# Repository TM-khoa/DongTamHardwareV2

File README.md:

# Hardware Air Cleaning Machine Valve Controller

# Hardware library

Download hardware library at this [repository](https://github.com/TM-khoa/KicadHardwareLibrary.git)
# Hardware description
## Powersource
- The system board is powered by a dual power supply, the AM22 AC-DC converter, which outputs both 24VDC and 5VDC.
- The power for the MCUs, LoRa module, and RS485 needs to be regulated to 3.3V using the LD1117-3.3 regulator.
- Other components can use the 5V output from the AM22.
- Two terminals—one for 5V and one for 24V—can be used to power the system board from an external DC supply.

## Control valve and fault detect
Each output pin of the Output Expander 74HC595 is connected to the Gate pin of an N-channel MOSFET (SI2302). The Source pin is connected to a 0.5 Ohm shunt resistor and to ground, while the Drain pin is connected to one terminal of the valve. The other valve terminal is connected to the 24V power supply.
	
An LM324 Op-Amp samples the voltage drop across the shunt resistor (approximately 300mV). This voltage is compared to a reference voltage to detect faults. A valve error occurs if there is no voltage drop.

To control 16 valves, two cascaded 74HC595 output expanders are required, with each output pin equipped with an indicator LED.

Each LM324 has four output pins, so four LM324 ICs are needed to monitor up to 16 valves. These outputs are connected to two cascaded 74HC165 input expanders and fed back to the MCU.

## Control LCD and LED bar

To interface the PCF8574 and 74HC595 pins (which require 5V at VIH) with the ESP32 (which outputs 3.3V at VOH), logic level shifters are needed on the I2C pins and the 74HC595 GPIO pins.

# STM32 pin table
| Pin Number | Pin Name | Function         | Device      | Description                   |
|------------|----------|------------------|-------------|-------------------------------|
| 2          | PC13     | GPIO_OUTPUT      | LED         |                               |
| 3          | PC14     | GPIO_INTERRUPT   | PCF8563     | Clock input interrupt          |
| 18         | PB0      | GPIO_INTERRUPT   | LORA RA-02  | LORA interrupt                 |
| 10         | PA0      | GPIO_OUTPUT      | LORA RA-02  | SPI2 Chip select               |
| 31         | PA10     | GPIO_OUTPUT      | SDcard      | SPI2 Chip select               |
| 25         | PB12     | GPIO_OUTPUT      | MCP41010    | SPI2 Chip select               |
| 26         | PB13     | SPI2_SCK             | LORA RA-02, Sdcard, MCP41010 |               |
| 27         | PB14     | SPI2_MISO             |             |                               |
| 28         | PB15     | SPI2_MOSI             |             |                               |
| 21         | PB10     | UART3_TX         | PC          | Log output data to desktop     |
| 22         | PB11     | UART3_RX         |             |                               |
| 45         | PB8      | I2C1_SCL         | PCF8563, AMS5915 |                           |
| 46         | PB9      | I2C1_SDA         |             |                               |
| 42         | PB6      | USART1_TX        | ESP32       |                               |
| 43         | PB7      | USART1_RX        |             |                               |
| 11         | PA1      | GPIO_OUTPUT      |             |                               |
| 12         | PA2      | USART2_TX        | SP3485      | RS485 communicate              |
| 13         | PA3      | USART2_RX        |             |                               |
| 32         | PA11     | USB_DM           | USB-C port  |                               |
| 32         | PA12     | USB_DP           |             |                               |
| 15         | PA5      | GPIO_OUTPUT      | 74HC595     | OutputExpander                |
| 16         | PA6      | GPIO_OUTPUT      |             |                               |
| 17         | PA7      | GPIO_OUTPUT      |             |                               |
| 39         | PB3      | GPIO_OUTPUT      | 74HC165     | InputExpander                 |
| 40         | PB4      | GPIO_OUTPUT      |             |                               |
| 41         | PB5      | GPIO_INPUT       |             |                               |
| 19         | PB1      | ADC              | HW685       | Read pressure from SP100       |

# ESP32 pin table

| Pin Number | Pin Name | Function   | Device     | Description                                |
|------------|----------|------------|------------|--------------------------------------------|
| 33         | IO21     | I2C_SDA    | PCF8574    | LCD20x4 Output Expander                    |
| 36         | IO22     | I2C_SCL    |            |                                            |
| 27         | IO16     | UART_RX    | STM32      |                                            |
| 28         | IO17     | UART_TX    |            |                                            |
| 4          | IO36     | GPIO_INPUT |            | Button from GUI user interface module      |
| 5          | IO39     | GPIO_INPUT |            |                                            |
| 6          | IO34     | GPIO_INPUT |            |                                            |
| 7          | IO35     | GPIO_INPUT |            |                                            |
| 29         | IO5      | GPIO_OUTPUT|            |                                            |
| 30         | IO18     | SPI_CLK    | 74HC595    | Control LED bar level                      |
| 31         | IO19     | SPI_MISO   |            |                                            |
| 37         | IO23     | SPI_MOSI   |            |                                            |

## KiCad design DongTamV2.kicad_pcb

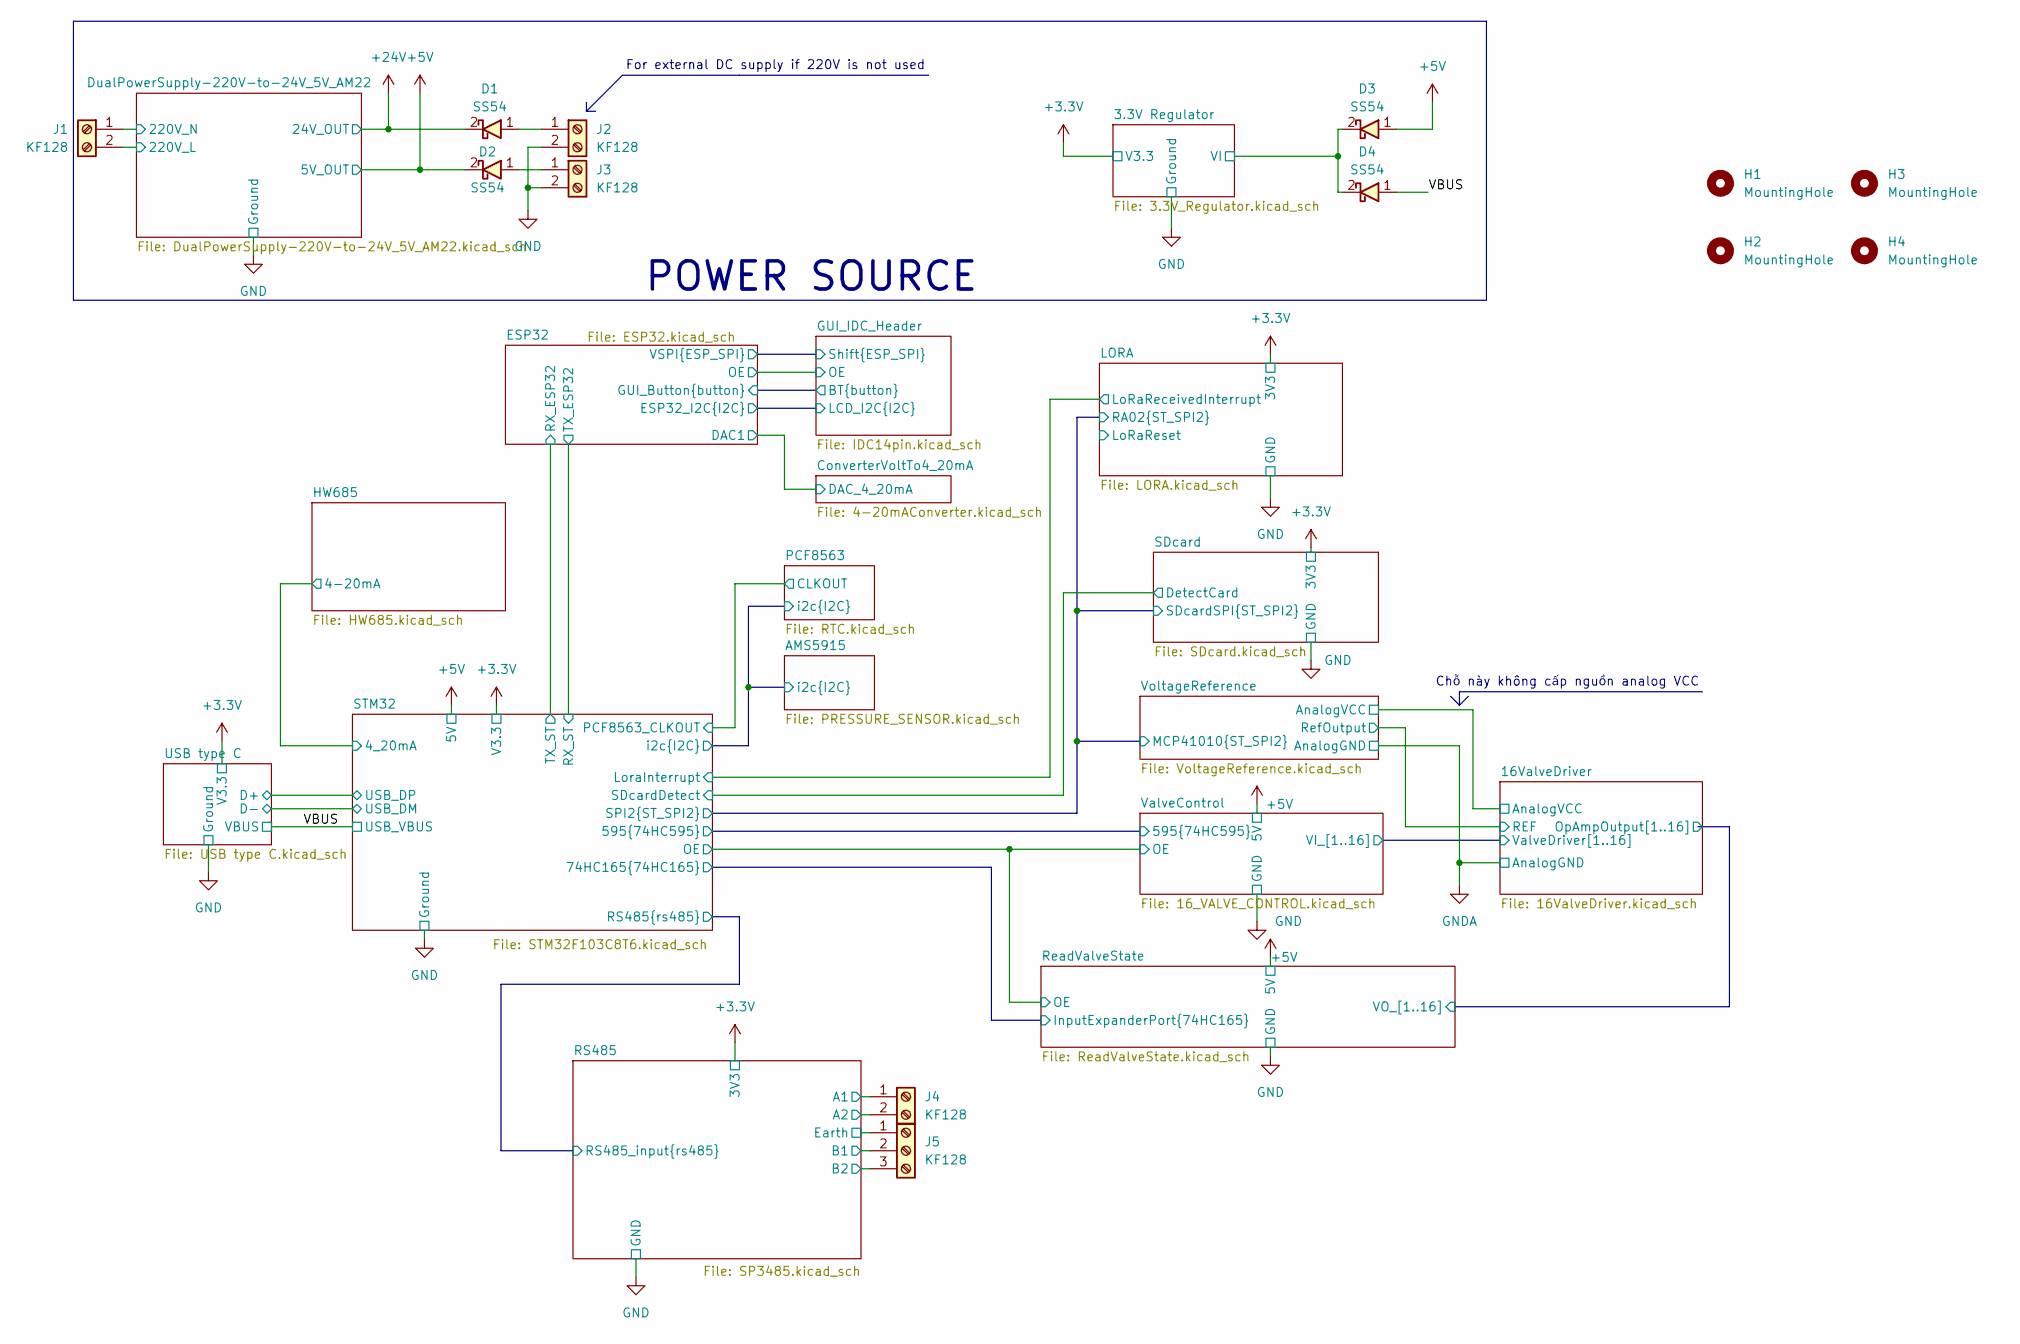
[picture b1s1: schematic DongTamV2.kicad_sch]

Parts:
D1, D2, D3, D4: SS54; Package-Diode-D_SMA
H1, H2, H3, H4: MountingHole; MountingHole_3.2mm_M3
J1, J2, J3, J4: KF128; TerminalBlock_bornier-2_P5.08mm
J5: KF128; TerminalBlock_bornier-3_P5.08mm

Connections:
+5V: D2.2, D3.1; also elsewhere on the board
+24V: D1.2; also elsewhere on the board
/3.3V Regulator/VI: D3.2, D4.2; also elsewhere on the board
/DualPowerSupply-220V-to-24V_5V_AM22/220V_L: J1.2; also elsewhere on the board
/DualPowerSupply-220V-to-24V_5V_AM22/220V_N: J1.1; also elsewhere on the board
/RS485/A_RS485: J4.1, J4.2; also elsewhere on the board
/RS485/B_RS485: J5.2, J5.3; also elsewhere on the board
/RS485/Earth: J5.1; also elsewhere on the board
/VBUS: D4.1; also elsewhere on the board
GND: J2.2, J3.2; also elsewhere on the board
unnamed: D1.1, J2.1
unnamed: D2.1, J3.1

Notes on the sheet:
POWER SOURCE
Chỗ này không cấp nguồn analog VCC
For external DC supply if 220V is not used

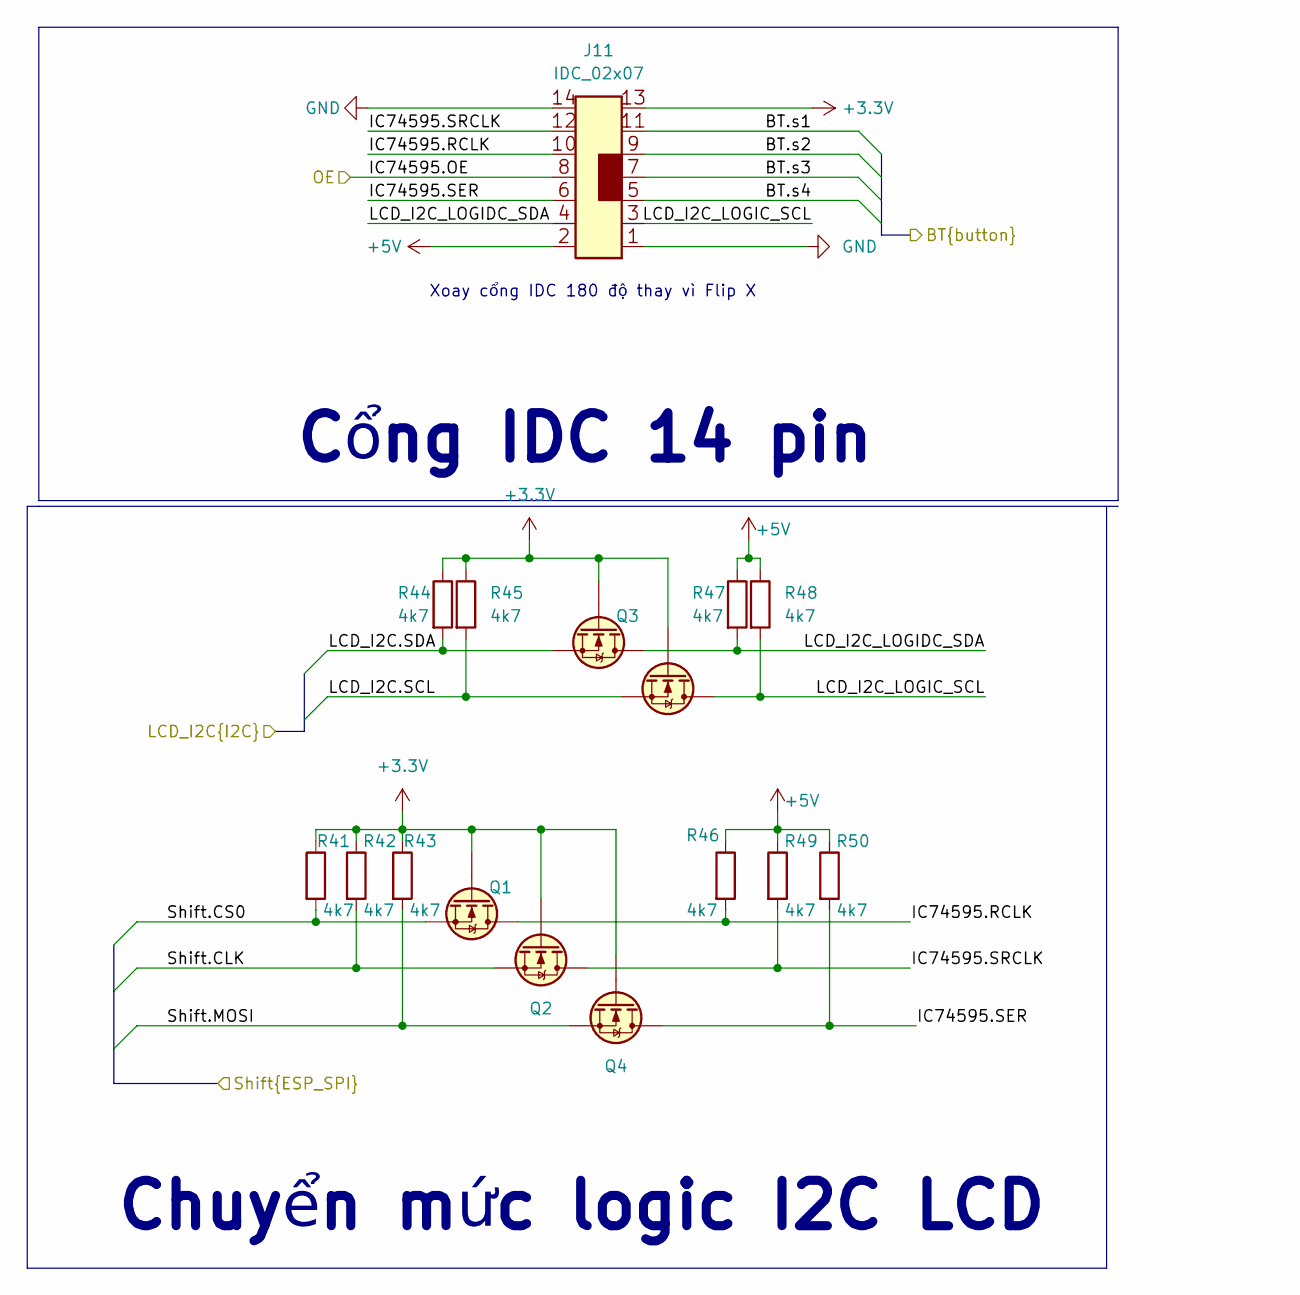
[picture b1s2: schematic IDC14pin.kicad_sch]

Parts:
J11: IDC_02x07; Conn-Vert-THT-2x7P-2.54mm-DC3
Q1, Q2, Q3, Q4, Q5: SI2302/BSS138; SOT23-3
R41, R42, R43, R44, R45, R46, R47, R48, R49, R50: 4k7; R_0603

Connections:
+3.3V: J11.13, Q1.1 (G), Q2.1 (G), Q3.1 (G), Q4.1 (G), Q5.1 (G), R41.1, R42.1, R43.1, R44.1, R45.1; also elsewhere on the board
+5V: J11.2, R46.1, R47.1, R48.1, R49.1, R50.1; also elsewhere on the board
/ESP32/ESP32_I2C.SCL: Q5.2 (S), R45.2; also elsewhere on the board
/ESP32/ESP32_I2C.SDA: Q3.2 (S), R44.2; also elsewhere on the board
/ESP32/GUI_Button.s1: J11.11; also elsewhere on the board
/ESP32/GUI_Button.s2: J11.9; also elsewhere on the board
/ESP32/GUI_Button.s3: J11.7; also elsewhere on the board
/ESP32/GUI_Button.s4: J11.5; also elsewhere on the board
/ESP32/VSPI.CLK: Q2.2 (S), R42.2; also elsewhere on the board
/ESP32/VSPI.CS0: Q1.2 (S), R41.2; also elsewhere on the board
/ESP32/VSPI.MOSI: Q4.2 (S), R43.2; also elsewhere on the board
/GUI_IDC_Header/IC74595.OE: J11.8; also elsewhere on the board
/GUI_IDC_Header/IC74595.RCLK: J11.10, Q1.3 (D), R46.2
/GUI_IDC_Header/IC74595.SER: J11.6, Q4.3 (D), R50.2
/GUI_IDC_Header/IC74595.SRCLK: J11.12, Q2.3 (D), R49.2
/GUI_IDC_Header/LCD_I2C_LOGIC_SCL: J11.3, Q5.3 (D), R48.2
/GUI_IDC_Header/LCD_I2C_LOGIDC_SDA: J11.4, Q3.3 (D), R47.2
GND: J11.1, J11.14; also elsewhere on the board

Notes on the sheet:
Chuyển mức logic I2C LCD
Xoay cổng IDC 180 độ thay vì Flip X
Cổng IDC 14 pin

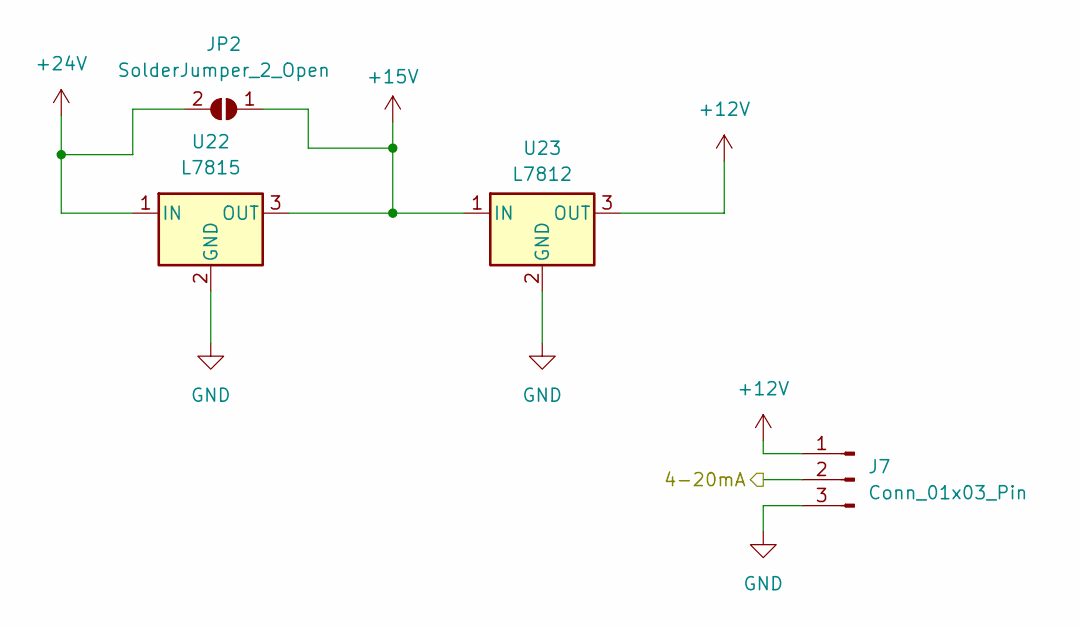
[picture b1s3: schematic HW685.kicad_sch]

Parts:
J7: Conn_01x03_Pin; PinHeader_1x03_P2.54mm_Vertical
JP2: SolderJumper_2_Open; SolderJumper-2_P1.3mm_Open_TrianglePad1.0x1.5mm
U22: L7815; Package-IC-Vert-SMD-TO_263-2_TabPin2
U23: L7812; Package-IC-Vert-SMD-TO_263-2_TabPin2

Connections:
+12V: J7.1, U23.3 (OUT)
+15V: JP2.1 (A), U22.3 (OUT), U23.1 (IN)
+24V: JP2.2 (B), U22.1 (IN); also elsewhere on the board
/HW685/4-20mA: J7.2; also elsewhere on the board
GND: J7.3, U22.2 (GND), U23.2 (GND); also elsewhere on the board

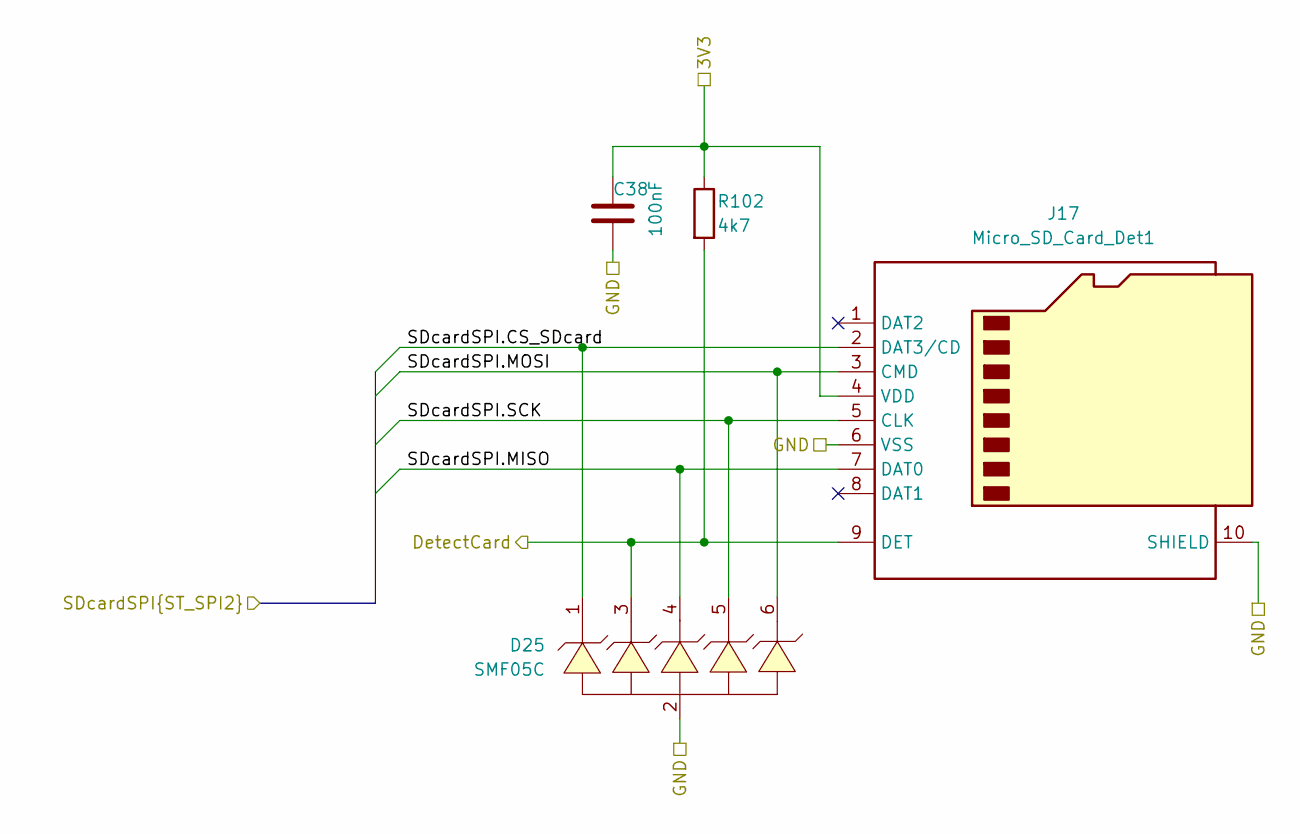
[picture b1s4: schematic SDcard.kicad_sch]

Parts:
C38: 100nF; C_0603
D25: SMF05C; Package-IC-TSSOP_6
J17: Micro_SD_Card_Det1; Socket_MicroSD-9P
R102: 4k7; R_0603

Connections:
+3.3V: C38.1, J17.4 (VDD), R102.1; also elsewhere on the board
/LORA/RA02.CS_SDcard: D25.1, J17.2 (DAT3/CD); also elsewhere on the board
/LORA/RA02.MISO: D25.4, J17.7 (DAT0); also elsewhere on the board
/LORA/RA02.MOSI: D25.6, J17.3 (CMD); also elsewhere on the board
/LORA/RA02.SCK: D25.5, J17.5 (CLK); also elsewhere on the board
/SDcard/DetectCard: D25.3, J17.9 (DET), R102.2; also elsewhere on the board
GND: C38.2, D25.2, J17.6 (VSS), J17.10 (SHIELD); also elsewhere on the board

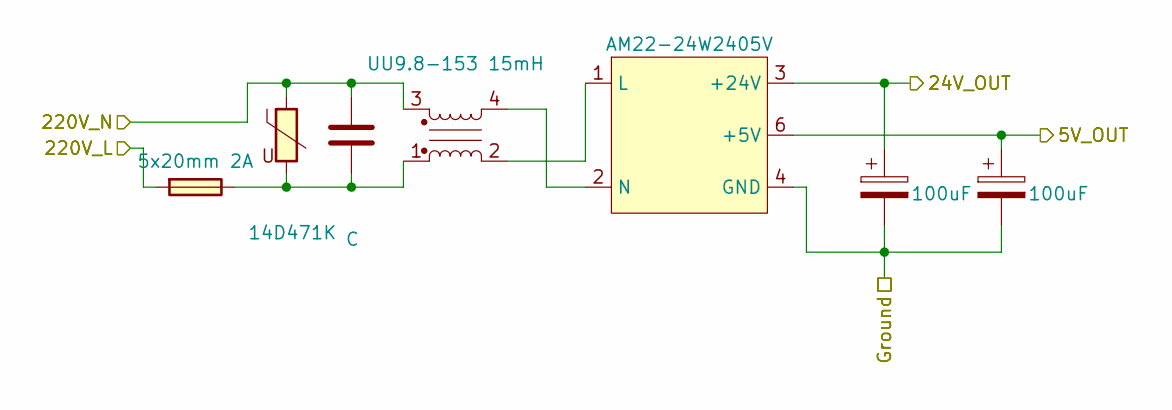
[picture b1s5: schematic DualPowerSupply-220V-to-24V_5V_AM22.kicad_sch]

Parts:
C1: C; C-Polyester-Rect-L16.5mm-W5.0mm-P15.00mm-MKT
C2, C3: 100uF; CP-Alu-SMD-8x10.5mm
F1: 5x20mm 2A; Fuse_BLX-A-P22.4mm
FL1: UU9.8-153 15mH; ACFilterChoke-UU9.8
RV1: 14D471K; RV_Disc_D12mm_W5.8mm_P7.5mm
U1: AM22-24W2405V; DualPowerSupply-24W_24V_05V_AM22

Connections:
+5V: C3.1, U1.6 (+5V); also elsewhere on the board
+24V: C2.1, U1.3 (+24V); also elsewhere on the board
/DualPowerSupply-220V-to-24V_5V_AM22/220V_L: F1.1; also elsewhere on the board
/DualPowerSupply-220V-to-24V_5V_AM22/220V_N: C1.1, FL1.3, RV1.1; also elsewhere on the board
GND: C2.2, C3.2, U1.4 (GND), U1.5 (GND); also elsewhere on the board
unnamed: C1.2, F1.2, FL1.1, RV1.2
unnamed: FL1.2, U1.1 (L)
unnamed: FL1.4, U1.2 (N)

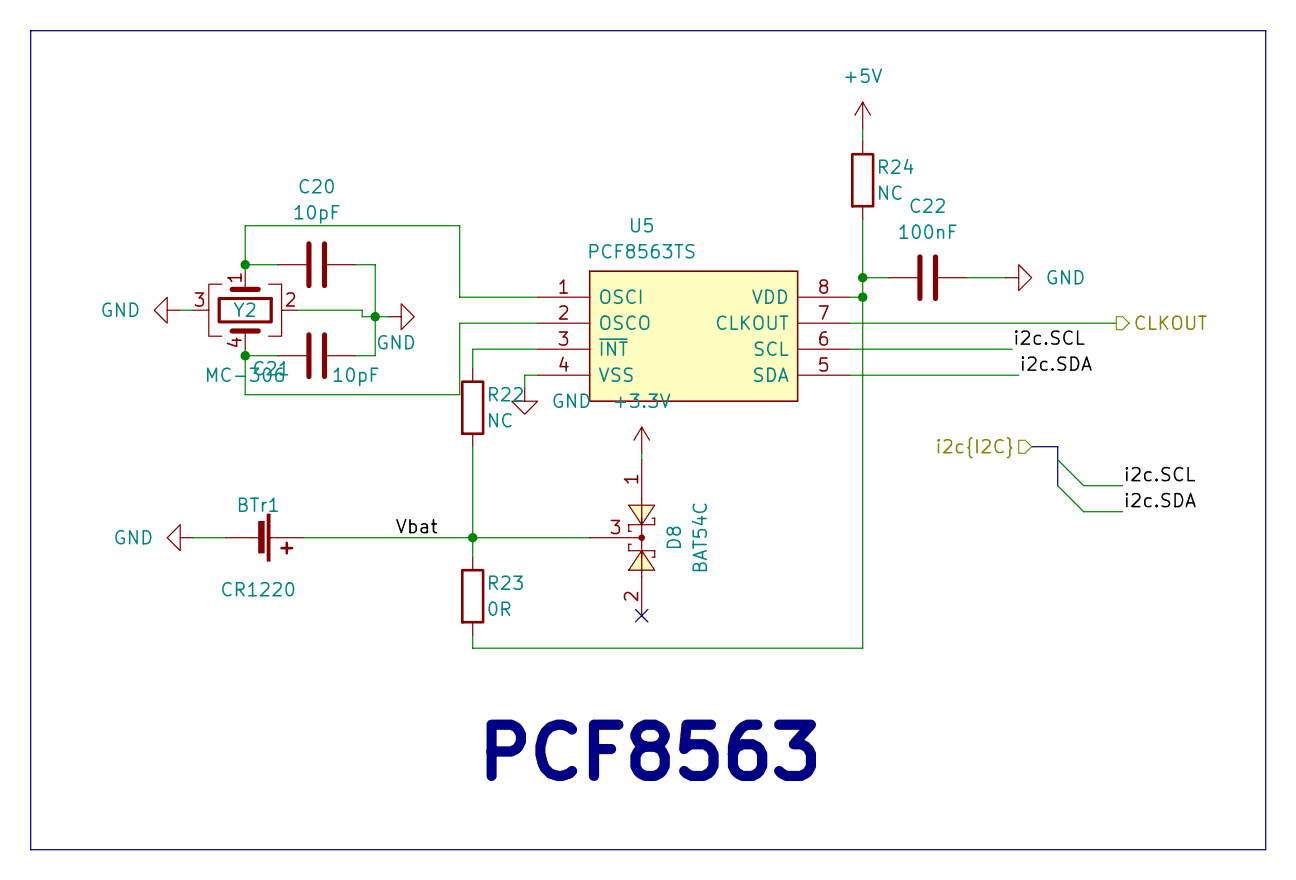
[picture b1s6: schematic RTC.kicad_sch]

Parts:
BTr1: CR1220; BatteryHolder-SMD-CR1220
C20, C21: 10pF; C_0603
C22: 100nF; C_0603
D8: BAT54C; SOT23-3
R22, R24: NC; R_0603
R23: 0R; R_0603
U5: PCF8563TS; Package-IC-Vert-SMD-1.27mm-8P-SOIC_8_Narrow_3.9x4.9mm; Mfg Part PCF8563TS/5,118
Y2: MC-306; Crystal_SMD_SeikoEpson_MC306-4Pin_8.0x3.2mm

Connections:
+3.3V: D8.1; also elsewhere on the board
+5V: R24.1; also elsewhere on the board
/AMS5915/i2c.SCL: U5.6 (SCL); also elsewhere on the board
/AMS5915/i2c.SDA: U5.5 (SDA); also elsewhere on the board
/PCF8563/CLKOUT: U5.7 (CLKOUT); also elsewhere on the board
/PCF8563/Vbat: BTr1.1 (+), D8.3, R22.2, R23.1
GND: BTr1.2 (-), C20.2, C21.2, C22.2, U5.4 (VSS), Y2.2, Y2.3; also elsewhere on the board
unnamed: C20.1, U5.1 (OSCI), Y2.1
unnamed: C21.1, U5.2 (OSCO), Y2.4
unnamed: C22.1, R23.2, R24.2, U5.8 (VDD)
unnamed: R22.1, U5.3 (~INT)

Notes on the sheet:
PCF8563

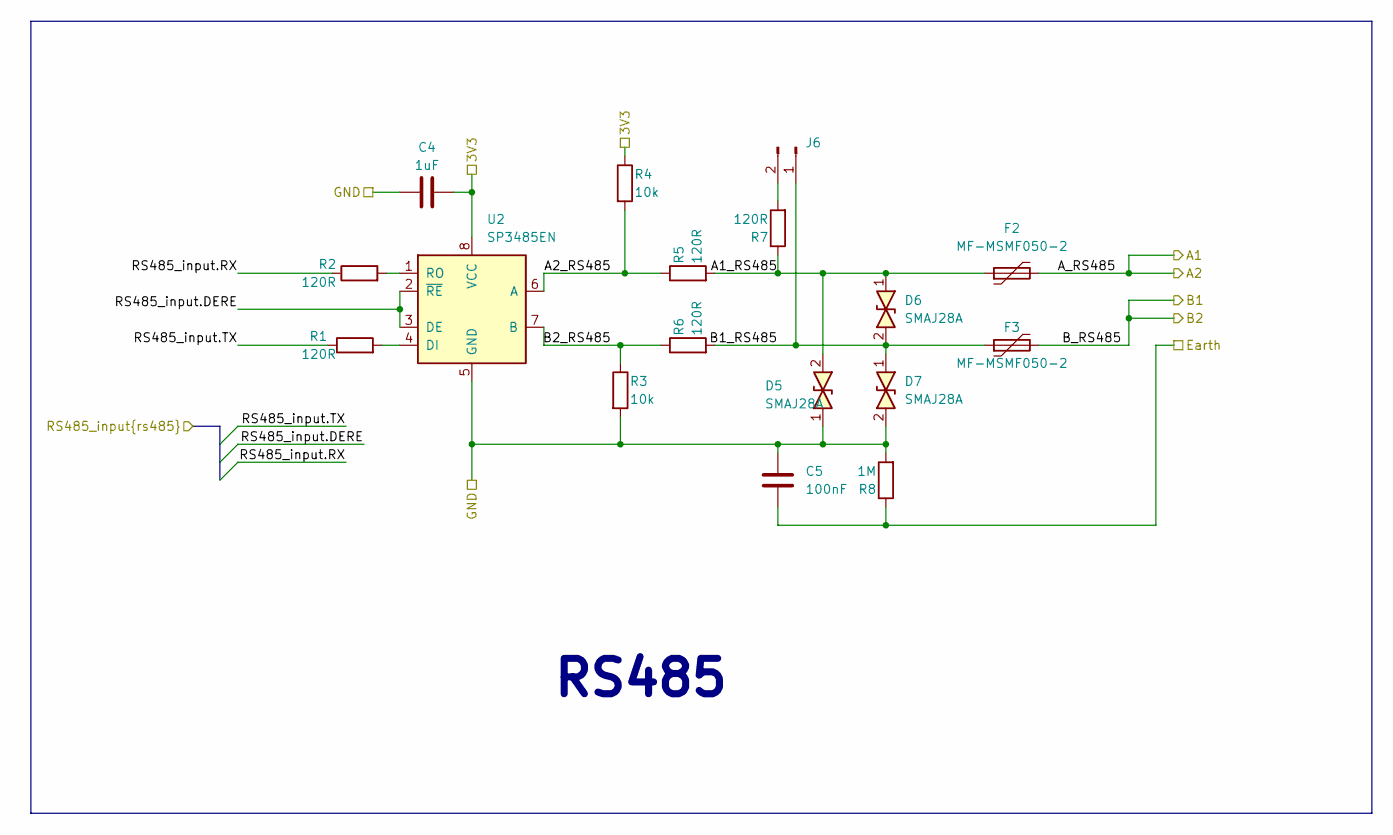
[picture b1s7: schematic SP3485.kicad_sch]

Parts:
C4: 1uF; C_0603
C5: 100nF; C_0603
D5, D6, D7: SMAJ28A; Package-Diode-D_SMA
F2, F3: MF-MSMF050-2; Fuse_1812_4532Metric
J6: Conn_01x02_Male; PinHeader_1x02_P2.54mm_Vertical
R1, R2, R5, R6, R7: 120R; R_0603
R3, R4: 10k; R_0603
R8: 1M; R_0603
U2: SP3485EN; Package-IC-Vert-SMD-1.27mm-8P-SOIC_8_Narrow_3.9x4.9mm

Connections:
+3.3V: C4.2, R4.1, U2.8 (VCC); also elsewhere on the board
/RS485/A1_RS485: D5.2, D6.1, F2.1, R5.2, R7.1
/RS485/A2_RS485: R4.2, R5.1, U2.6 (A)
/RS485/A_RS485: F2.2; also elsewhere on the board
/RS485/B1_RS485: D6.2, D7.1, F3.1, J6.1, R6.2
/RS485/B2_RS485: R3.1, R6.1, U2.7 (B)
/RS485/B_RS485: F3.2; also elsewhere on the board
/RS485/Earth: C5.1, R8.1; also elsewhere on the board
/RS485/RS485_input.DERE: U2.2 (~RE), U2.3 (DE); also elsewhere on the board
/RS485/RS485_input.RX: R2.1; also elsewhere on the board
/RS485/RS485_input.TX: R1.1; also elsewhere on the board
GND: C4.1, C5.2, D5.1, D7.2, R3.2, R8.2, U2.5 (GND); also elsewhere on the board
unnamed: J6.2, R7.2
unnamed: R1.2, U2.4 (DI)
unnamed: R2.2, U2.1 (RO)

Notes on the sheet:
RS485

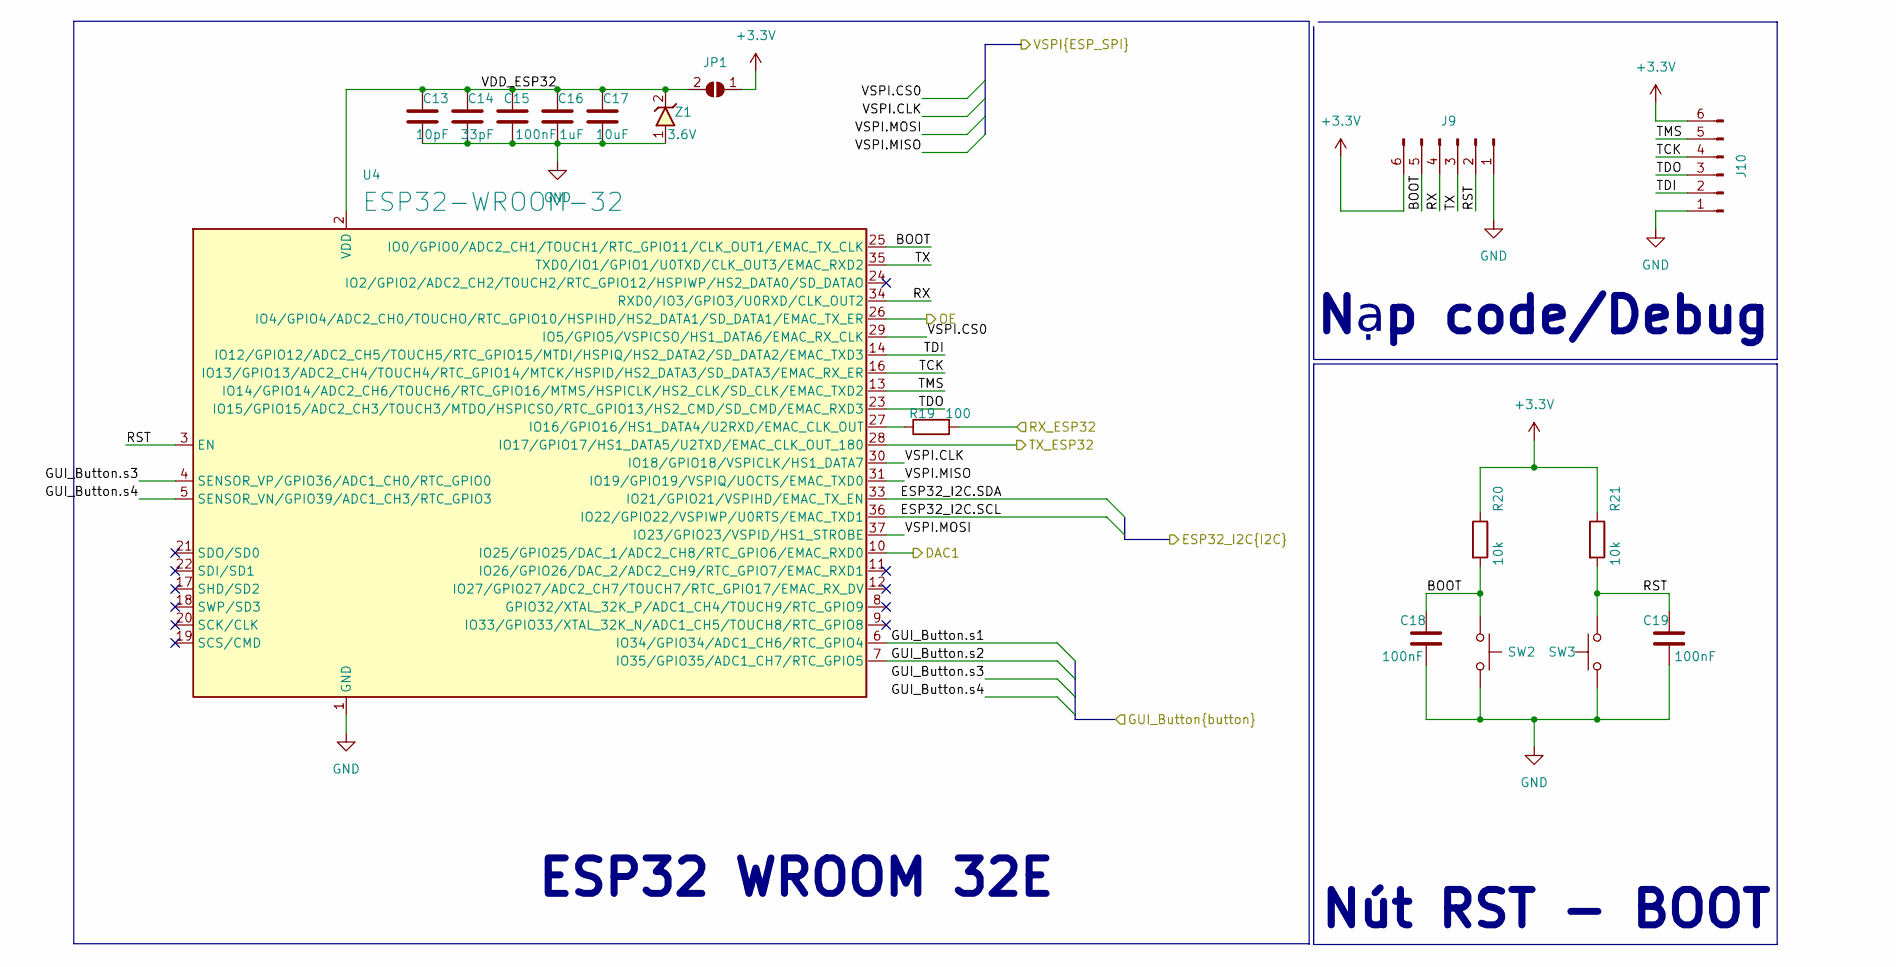
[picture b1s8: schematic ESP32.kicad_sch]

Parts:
C13: 10pF; C_0603
C14: 33pF; C_0603
C15, C18, C19: 100nF; C_0603
C16: 1uF; C_0603
C17: 10uF; C_0603
J9, J10: Conn_01x05_Male; PinHeader_1x06_P2.54mm_Vertical
JP1: SolderJumper-2_P1.3mm_Open_RoundedPad1.0x1.5mm
R19: 100; R_0603
R20, R21: 10k; R_0603
SW2, SW3: PTS810; ButtonPush-Vert-SMD-4P-SPST_PTS810
U4: ESP32-WROOM-32
Z1: 3.6V; Package-Diode-D_MiniMELF

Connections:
+3.3V: J9.6, J10.6, JP1.1 (A), R20.1, R21.1; also elsewhere on the board
/ConverterVoltTo4_20mA/DAC_4_20mA: U4.10 (IO25/GPIO25/DAC_1/ADC2_CH8/RTC_GPIO6/EM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); also elsewhere on the board
/ESP32/BOOT: C18.1, J9.5, R20.2, SW2.1, U4.25 (IO0/GPIO0/ADC2_CH1/TOUCH1/RTC_GPIO11/CL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)
/ESP32/ESP32_I2C.SCL: U4.36 (IO22/GPIO22/VSPIWP/U0RTS/EMAC_TXD1); also elsewhere on the board
/ESP32/ESP32_I2C.SDA: U4.33 (IO21/GPIO21/VSPIHD/EMAC_TX_EN); also elsewhere on the board
/ESP32/GUI_Button.s1: U4.6 (IO34/GPIO34/ADC1_CH6/RTC_GPIO4); also elsewhere on the board
/ESP32/GUI_Button.s2: U4.7 (IO35/GPIO35/ADC1_CH7/RTC_GPIO5); also elsewhere on the board
/ESP32/GUI_Button.s3: U4.4 (SENSOR_VP/GPIO36/ADC1_CH0/RTC_GPIO0); also elsewhere on the board
/ESP32/GUI_Button.s4: U4.5 (SENSOR_VN/GPIO39/ADC1_CH3/RTC_GPIO3); also elsewhere on the board
/ESP32/RST: C19.1, J9.2, R21.2, SW3.2, U4.3 (EN)
/ESP32/RX: J9.4, U4.34 (RXD0/IO3/GPIO3/U0RXD/CLK_OUT2)
/ESP32/RX_ESP32: R19.2; also elsewhere on the board
/ESP32/TCK: J10.4, U4.16 (IO13/GPIO13/ADC2_CH4/TOUCH4/RTC_GPIO14/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)
/ESP32/TDI: J10.2, U4.14 (IO12/GPIO12/ADC2_CH5/TOUCH5/RTC_GPIO15/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)
/ESP32/TDO: J10.3, U4.23 (IO15/GPIO15/ADC2_CH3/TOUCH3/MTDO/HSPICS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)
/ESP32/TMS: J10.5, U4.13 (IO14/GPIO14/ADC2_CH6/TOUCH6/RTC_GPIO16/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)
/ESP32/TX: J9.3, U4.35 (TXD0/IO1/GPIO1/U0TXD/CLK_OUT3/EMAC_RXD2)
/ESP32/TX_ESP32: U4.28 (IO17/GPIO17/HS1_DATA5/U2TXD/EMAC_CLK_OU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); also elsewhere on the board
/ESP32/VDD_ESP32: C13.1, C14.1, C15.1, C16.1, C17.1, JP1.2 (B), U4.2 (VDD), Z1.2
/ESP32/VSPI.CLK: U4.30 (IO18/GPIO18/VSPICLK/HS1_DATA7); also elsewhere on the board
/ESP32/VSPI.CS0: U4.29 (IO5/GPIO5/VSPICSO/HS1_DATA6/EMAC_RX_CLK); also elsewhere on the board
/ESP32/VSPI.MISO: U4.31 (IO19/GPIO19/VSPIQ/UOCTS/EMAC_TXD0)
/ESP32/VSPI.MOSI: U4.37 (IO23/GPIO23/VSPID/HS1_STROBE); also elsewhere on the board
/GUI_IDC_Header/IC74595.OE: U4.26 (IO4/GPIO4/ADC2_CH0/TOUCHO/RTC_GPIO10/HS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); also elsewhere on the board
GND: C13.2, C14.2, C15.2, C16.2, C17.2, C18.2, C19.2, J9.1, J10.1, SW2.2, SW3.1, U4.1 (GND), U4.15 (GND), U4.38 (GND), U4.39 (GND), Z1.1; also elsewhere on the board
unnamed: R19.1, U4.27 (IO16/GPIO16/HS1_DATA4/U2RXD/EMAC_CLK_OUT)

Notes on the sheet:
ESP32 WROOM 32E
Nạp code/Debug
Nút RST - BOOT

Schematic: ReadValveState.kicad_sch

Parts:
C36, C37: 100nF; C_0603
U15, U16: 74HC165; Package-IC-Vert-SMD-1.27mm-16P-SOIC_16_Narrow_3.92x10.2mm

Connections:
+5V: C36.2, C37.2, U15.16 (VCC), U16.16 (VCC); also elsewhere on the board
/16ValveDriver/OpAmpOutput1: U16.11 (D0); also elsewhere on the board
/16ValveDriver/OpAmpOutput2: U16.12 (D1); also elsewhere on the board
/16ValveDriver/OpAmpOutput3: U16.13 (D2); also elsewhere on the board
/16ValveDriver/OpAmpOutput4: U16.14 (D3); also elsewhere on the board
/16ValveDriver/OpAmpOutput5: U16.3 (D4); also elsewhere on the board
/16ValveDriver/OpAmpOutput6: U16.4 (D5); also elsewhere on the board
/16ValveDriver/OpAmpOutput7: U16.5 (D6); also elsewhere on the board
/16ValveDriver/OpAmpOutput8: U16.6 (D7); also elsewhere on the board
/16ValveDriver/OpAmpOutput9: U15.11 (D0); also elsewhere on the board
/16ValveDriver/OpAmpOutput10: U15.12 (D1); also elsewhere on the board
/16ValveDriver/OpAmpOutput11: U15.13 (D2); also elsewhere on the board
/16ValveDriver/OpAmpOutput12: U15.14 (D3); also elsewhere on the board
/16ValveDriver/OpAmpOutput13: U15.3 (D4); also elsewhere on the board
/16ValveDriver/OpAmpOutput14: U15.4 (D5); also elsewhere on the board
/16ValveDriver/OpAmpOutput15: U15.5 (D6); also elsewhere on the board
/16ValveDriver/OpAmpOutput16: U15.6 (D7); also elsewhere on the board
/ReadValveState/74HC165_CascadeDATA: U15.9 (Q7), U16.10 (DS)
/ReadValveState/InputExpanderPort.DATA: U16.9 (Q7); also elsewhere on the board
/ReadValveState/InputExpanderPort.LOAD: U15.1 (~PL), U16.1 (~PL); also elsewhere on the board
/ReadValveState/InputExpanderPort.SCK: U15.2 (CP), U16.2 (CP); also elsewhere on the board
/ReadValveState/OE: U15.15 (~CE), U16.15 (~CE); also elsewhere on the board
GND: C36.1, C37.1, U15.8 (GND), U16.8 (GND); also elsewhere on the board

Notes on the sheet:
74HC165

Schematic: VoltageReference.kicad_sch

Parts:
RV2: TC33X_10k; Potentiometer-Vert-SMD-3P-Bourns_TC33X

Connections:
/16ValveDriver/AnalogVCC: RV2.3; also elsewhere on the board
/16ValveDriver/REF: RV2.2; also elsewhere on the board
GNDA: RV2.1; also elsewhere on the board

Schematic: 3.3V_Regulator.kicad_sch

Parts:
C28, C31: 100nF; C_0805
C29, C30: 10uF; C_0805
U10: LD1117; SOT233

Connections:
+3.3V: C30.1, C31.1, U10.2 (VO); also elsewhere on the board
/3.3V Regulator/VI: C28.1, C29.1, U10.3 (VI); also elsewhere on the board
GND: C28.2, C29.2, C30.2, C31.2, U10.1 (GND); also elsewhere on the board

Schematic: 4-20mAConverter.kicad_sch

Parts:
C39: 100nF; C_0603
D26: SS54; Package-Diode-D_SMA
J18: HT3.96mm-3P; TerminalBlock_bornier-3_P5.08mm
LE19: Blue 0603; LED_0603
LE20: LED 0805; LED_0805
Q22: MMBT3904; SOT23-3
R103: 220R; R_0603
R104: 1k; R_0603
R105: 10k; R_0603
R106: 560R; R_0603
R107, R108: 100k; R_0603
R109, R110, R111, R112, R113, R114, R117: 820k; R_0603
R115: 100R; R_0603
R116: 680k; R_0603
RV3, RV4: 100k; Potentiometer-Vert-THT-Bourns_3296W
U18: LM324; Package-IC-Vert-SMD-1.27mm-14P-SOIC_14_Narrow_3.9x8.7mm
U19: LM317_TO-252; Package-IC-Vert-SMD-TO_252_2
U20: TL431; SOT23-3

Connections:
/ConverterVoltTo4_20mA/DAC_4_20mA: R107.1, U18.3 (+); also elsewhere on the board
/ConverterVoltTo4_20mA/LM137_IN: C39.1, D26.2, Q22.3 (C), U18.4 (V+), U19.3 (VI)
/ConverterVoltTo4_20mA/LM137_OUT: R103.1, R105.1, R106.2, U19.2 (VO)
/ConverterVoltTo4_20mA/TransB: Q22.1 (B), U18.8
GND: C39.2, J18.1, LE19.2, R104.2, R107.2, R111.2, R112.2, RV3.3, RV4.3, U18.11 (V-), U20.3 (A); also elsewhere on the board
unnamed: J18.2, LE20.2
unnamed: LE19.1, R105.2
unnamed: LE20.1, R115.1, R117.2
unnamed: Q22.2 (E), R113.2, R115.2
unnamed: R108.1, RV3.1
unnamed: R109.1, RV4.2
unnamed: R114.2, R116.1, U18.7
unnamed: RV4.1, U18.1, U18.2 (-)
unnamed: R109.2, R110.1, U18.5 (+)
unnamed: R111.1, R114.1, U18.6 (-)
unnamed: R116.2, R117.1, U18.10 (+)
unnamed: R112.1, R113.1, U18.9 (-)
unnamed: RV3.2, U18.12 (+)
unnamed: R110.2, U18.13 (-), U18.14
unnamed: R103.2, R104.1, U19.1 (ADJ)
unnamed: R106.1, R108.2, U20.1 (K), U20.2 (REF)
VCC: D26.1, J18.3

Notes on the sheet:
0-3v3 -> 4-20mA

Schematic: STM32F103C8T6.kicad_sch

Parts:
C6, C8: 22pF; C_0603
C7: 10pF; C_0603
C9, C10, C11, C12: 100nF; C_0603
J8: Conn-Vert-THT-2.54mm-2x4P-IDC_Header
LE1, LE2: Blue 0603; LED_0603
R9: 1M; R_0603
R10, R14: 10k; R_0603
R11, R12: 4k7; R_0603
R13, R16, R120: 1k; R_0603
R15: 10K; R_0603
R17, R18: ?; R_0603
SW1: PTS810; ButtonPush-Vert-SMD-4P-SPST_PTS810
U3: MCU_STM32F103C8Tx; Package-IC-LQFP-48P-7x7mm-P0.5mm
Y1: 16MHz; Crystal-SMD-4P-3.2x2.6mm-3225

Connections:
+3.3V: C9.1, C10.1, C11.1, C12.1, J8.1 (3V3), LE1.1, LE2.1, R10.1, R11.1, R12.1, R120.2, U3.1 (VBAT), U3.9 (VDDA), U3.24 (VDD), U3.36 (VDD), U3.48 (VDD); also elsewhere on the board
+5V: J8.2 (5V); also elsewhere on the board
/AMS5915/i2c.SCL: R11.2, U3.45 (PB8/TIM4_CH3/I2C1_SCL/CANRX); also elsewhere on the board
/AMS5915/i2c.SDA: R12.2, U3.46 (PB9/TIM4_CH4/I2C1_SDA/CANTX); also elsewhere on the board
/ESP32/RX_ESP32: U3.42 (PB6/USART1_TX/I2C1_SCL/TIM4_CH1); also elsewhere on the board
/ESP32/TX_ESP32: U3.43 (PB7/USART1_RX/I2C1_SDA/TIM4_CH2); also elsewhere on the board
/HW685/4-20mA: U3.19 (PB1/ADC12_IN9/TIM3_CH4/TIM1_CH3N); also elsewhere on the board
/LORA/LoRaReceivedInterrupt: U3.18 (PB0/ADC12_IN8/TIM3_CH3/TIM1_CH2N); also elsewhere on the board
/LORA/RA02.CS_LORA: U3.10 (PA0/WKUP/USART2_CTS/ADC12_IN0/TIM2_CH1_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); also elsewhere on the board
/LORA/RA02.CS_MCP41010: U3.25 (PB12/SPI2_NSS/I2C2_SMBAI/USART3_CK/TIM1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); also elsewhere on the board
/LORA/RA02.CS_SDcard: U3.31 (PA10/USART1_RX/TIM1_CH3); also elsewhere on the board
/LORA/RA02.MISO: U3.27 (PB14/SPI2_MISO/USART3_RTS/TIM1_CH2N); also elsewhere on the board
/LORA/RA02.MOSI: U3.28 (PB15/SPI2_MOSI/TIM1_CH3N); also elsewhere on the board
/LORA/RA02.SCK: U3.26 (PB13/SPI2_SCK/USART3_CTS/TIM1_CH1N); also elsewhere on the board
/PCF8563/CLKOUT: R16.1, R120.1, U3.3 (PC14/OSC32_IN); also elsewhere on the board
/RS485/RS485_input.DERE: U3.11 (PA1/USART2_RTS/ADC12_IN1/TIM2_CH2); also elsewhere on the board
/RS485/RS485_input.RX: U3.13 (PA3/USART2_RX/ADC12_IN3/TIM2_CH4); also elsewhere on the board
/RS485/RS485_input.TX: U3.12 (PA2/USART2_TX/ADC12_IN2/TIM2_CH3); also elsewhere on the board
/ReadValveState/InputExpanderPort.DATA: U3.39 (PB3/JTDO/TIM2_CH2/TRACESWO/SPI1_SCK); also elsewhere on the board
/ReadValveState/InputExpanderPort.LOAD: U3.41 (PB5/TIM3_CH2/SPI1_MOSI/I2C1_SMBAI); also elsewhere on the board
/ReadValveState/InputExpanderPort.SCK: U3.40 (PB4/JNTRST/TIM3_CH1/SPI1_MISO); also elsewhere on the board
/ReadValveState/OE: U3.29 (PA8/USART1_CK/TIM1_CH1/MCO); also elsewhere on the board
/SDcard/DetectCard: U3.14 (PA4/SPI1_NSS/USART2_CK/ADC12_IN4); also elsewhere on the board
/STM32/595.RCLK: U3.16 (PA6/SPI1_MISO/ADC12_IN6/TIM3_CH1); also elsewhere on the board
/STM32/595.SER: U3.17 (PA7/SPI1_MOSI/ADC12_IN7/TIM3_CH2); also elsewhere on the board
/STM32/595.SRCLK: U3.15 (PA5/SPI1_SCK/ADC12_IN5); also elsewhere on the board
/STM32/BOOT0: R15.2, U3.44 (BOOT0)
/STM32/LED: R13.1, U3.2 (PC13/TAMPER-RTC)
/STM32/PC15: U3.4 (PC15/OSC32_OUT)
/STM32/PD0: C6.2, R9.1, U3.5 (PD0/OSC_IN), Y1.1
/STM32/PD1: C8.1, R9.2, U3.6 (PD1/OSC_OUT), Y1.3
/STM32/RST: C7.2, R10.2, SW1.1, U3.7 (NRST)
/STM32/RX_LOG: J8.8 (RX), U3.22 (PB11/I2C2_SDA/USART3_RX/TIM2_CH4)
/STM32/SWCLK: J8.7 (SWCLK), U3.37 (PA14/JTCK/SWCLK)
/STM32/SWDIO: J8.5 (SWDIO), U3.34 (PA13/JTMS/SWDIO)
/STM32/TX_LOG: J8.6 (TX), U3.21 (PB10/I2C2_SCL/USART3_TX/TIM2_CH3)
/STM32/USB_DM: U3.32 (PA11/USART1_CTS/CANRX/USBDM/TIM1_CH4); also elsewhere on the board
/STM32/USB_DP: U3.33 (PA12/USART1_RTS/CANTX/USBDP/TIM1_ETR); also elsewhere on the board
/STM32/USB_Detect: R17.1, R18.2, U3.30 (PA9/USART1_TX/TIM1_CH2)
/VBUS: R17.2; also elsewhere on the board
GND: C6.1, C7.1, C8.2, C9.2, C10.2, C11.2, C12.2, J8.3 (GND), J8.4 (GND), R14.1, R15.1, R18.1, SW1.2, U3.8 (VSSA), U3.23 (VSS), U3.35 (VSS), U3.47 (VSS), Y1.2, Y1.4; also elsewhere on the board
unnamed: LE1.2, R13.2
unnamed: LE2.2, R16.2
unnamed: R14.2, U3.20 (PB2/BOOT1)

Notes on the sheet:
TỤ LỌC NGUỒN
STM32F103C8T6
Kết nối trực tiếp, không đảo
HEADER nạp và debug
THẠCH ANH
Tham khảo tài liệu ST về USB
V2.0.0 Change log: Chân OE của PA12 đổi sang PA8 chân 74HC165.LOAD của PA11 đổi sang PB5 Chân 595.RCLK đổi thành PA6 để tận dụng bus SPI đi chung với nhau i2c.SCL và SDA đổi sang PB8 và PB9 TX_ST và RX_ST đổi sang PB6 và PB7 PA9 dùng cho VBUS sensing PA5 dùng để detect SDcard
Tận dụng bus SPI đi chung với nhau, có thể dùng để test giao tiếp SPI nếu không dùng chức năng HC595
BUS

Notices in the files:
parts and their libraries:
Copyright 2021 Accelerated Designs. All rights reserved.
